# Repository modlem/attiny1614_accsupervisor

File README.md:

# attiny1614_accsupervisor
Relay Service Module Design Files

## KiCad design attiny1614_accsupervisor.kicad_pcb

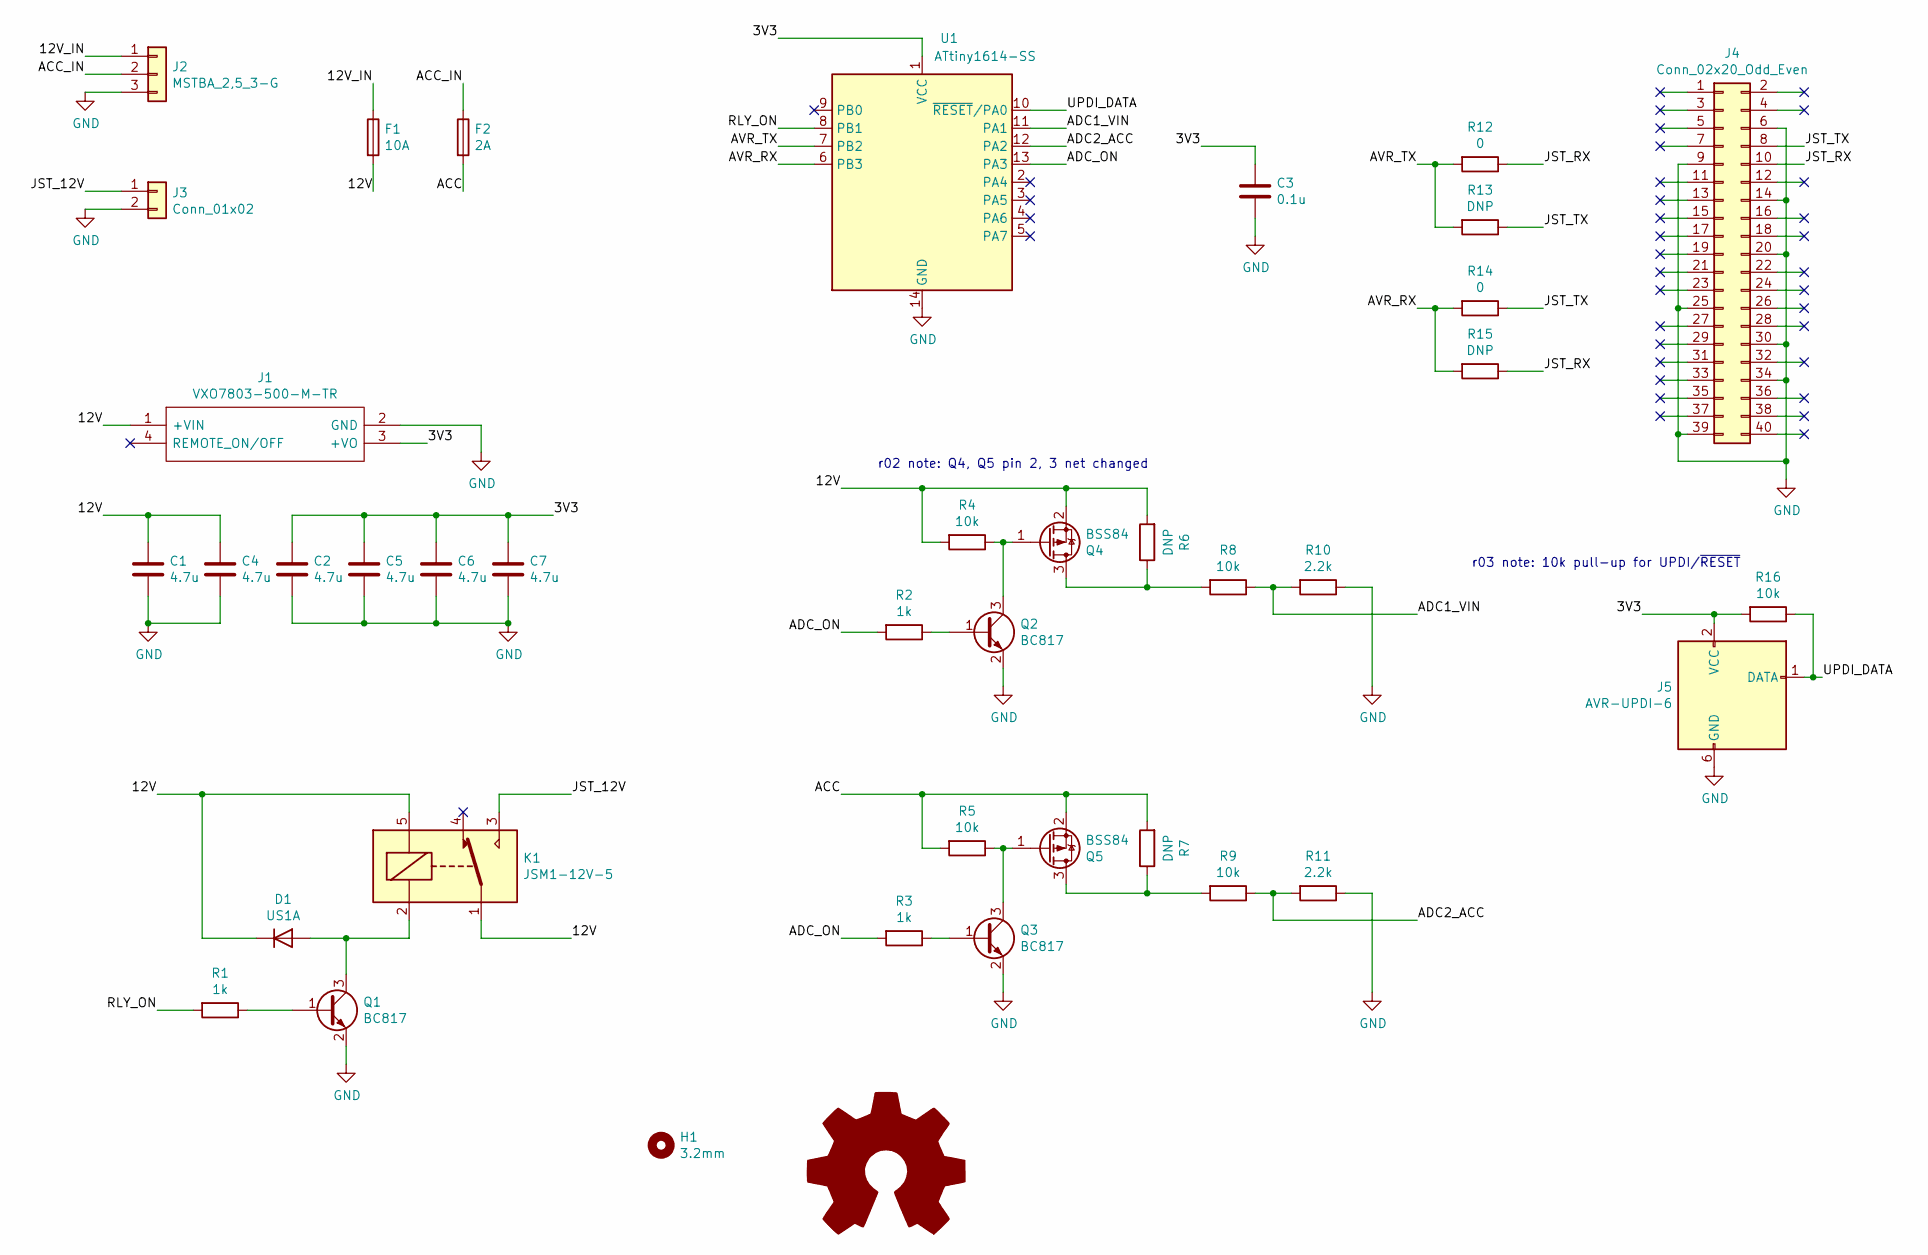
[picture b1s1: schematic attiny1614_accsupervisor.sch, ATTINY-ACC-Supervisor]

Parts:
C1, C2, C4, C5, C6, C7: 4.7u; C_0805_2012Metric_Pad1.15x1.40mm_HandSolder; Manufacturer_Part_Number 0805X475M250CT
C3: 0.1u; C_1206_3216Metric_Pad1.42x1.75mm_HandSolder
D1: US1A; D_SMA; Manufacturer_Part_Number US1A-13-F
F1: 10A; Fuseholder_Cylinder-5x20mm_Geoyoung_GF-205B; Manufacturer_Part_Number (10A)
F2: 2A; Fuseholder_Cylinder-5x20mm_Geoyoung_GF-205B
H1: 3.2mm; MountingHole_3.2mm_M3
J1: VXO7803-500-M-TR; VXO7803500MTR; Mouser Part Number 490-VXO7803-500-M-TR
J2: MSTBA_2,5_3-G; PhoenixContact_MSTBA_2,5_3-G_1x03_P5.00mm_Horizontal
J3: Conn_01x02; TerminalBlock_Phoenix_PT-1,5-2-5.0-H_1x02_P5.00mm_Horizontal
J4: Conn_02x20_Odd_Even; PinHeader_2x20_P2.54mm_Vertical
J5: AVR-UPDI-6; PinHeader_2x03_P2.54mm_Vertical
K1: JSM1-12V-5; Relay_SPDT_Omron-G5LE-1; Manufacturer_Part_Number JSM1-12V-5
Q1, Q2, Q3: BC817; SOT-23; Manufacturer_Part_Number BC817-25,215
Q4, Q5: BSS84; SOT-23; Manufacturer_Part_Number BSS84-7-F
R1, R2, R3: 1k; R_1206_3216Metric_Pad1.42x1.75mm_HandSolder; Manufacturer_Part_Number (1k)
R4, R5, R8, R9, R16: 10k; R_1206_3216Metric_Pad1.42x1.75mm_HandSolder; Manufacturer_Part_Number (10k)
R6, R7, R13, R15: DNP; R_1206_3216Metric_Pad1.42x1.75mm_HandSolder
R10, R11: 2.2k; R_1206_3216Metric_Pad1.42x1.75mm_HandSolder; Manufacturer_Part_Number (2.2k)
R12, R14: 0; R_1206_3216Metric_Pad1.42x1.75mm_HandSolder; Manufacturer_Part_Number (0)
U1: ATtiny1614-SS; SOIC-14_3.9x8.7mm_P1.27mm

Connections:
/3V3: C2.1, C3.1, C5.1, C6.1, C7.1, J1.3 (+VO), J5.2 (VCC), R16.2, U1.1 (VCC)
/12V: C1.1, C4.1, D1.1 (K), F1.2, J1.1 (+VIN), K1.1, K1.5, Q4.2 (S), R4.2, R6.2
/12V_IN: F1.1, J2.1
/ACC: F2.2, Q5.2 (S), R5.2, R7.2
/ACC_IN: F2.1, J2.2
/ADC1_VIN: R8.1, R10.2, U1.11 (PA1)
/ADC2_ACC: R9.1, R11.2, U1.12 (PA2)
/ADC_ON: R2.2, R3.2, U1.13 (PA3)
/AVR_RX: R14.2, R15.2, U1.6 (PB3)
/AVR_TX: R12.2, R13.2, U1.7 (PB2)
/JST_12V: J3.1, K1.3
/JST_RX: J4.10, R12.1, R15.1
/JST_TX: J4.8, R13.1, R14.1
/RLY_ON: R1.2, U1.8 (PB1)
/UPDI_DATA: J5.1 (DATA), R16.1, U1.10 (~RESET~/PA0)
GND: C1.2, C2.2, C3.2, C4.2, C5.2, C6.2, C7.2, J1.2 (GND), J2.3, J3.2, J4.6, J4.9, J4.14, J4.20, J4.25, J4.30, J4.34, J4.39, J5.6 (GND), Q1.2 (E), Q2.2 (E), Q3.2 (E), R10.1, R11.1, U1.14 (GND)
unnamed: D1.2 (A), K1.2, Q1.3 (C)
unnamed: Q1.1 (B), R1.1
unnamed: Q2.1 (B), R2.1
unnamed: Q2.3 (C), Q4.1 (G), R4.1
unnamed: Q3.1 (B), R3.1
unnamed: Q3.3 (C), Q5.1 (G), R5.1
unnamed: Q4.3 (D), R6.1, R8.2
unnamed: Q5.3 (D), R7.1, R9.2

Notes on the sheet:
r02 note: Q4, Q5 pin 2, 3 net changed
r03 note: 10k pull-up for UPDI/~RESET

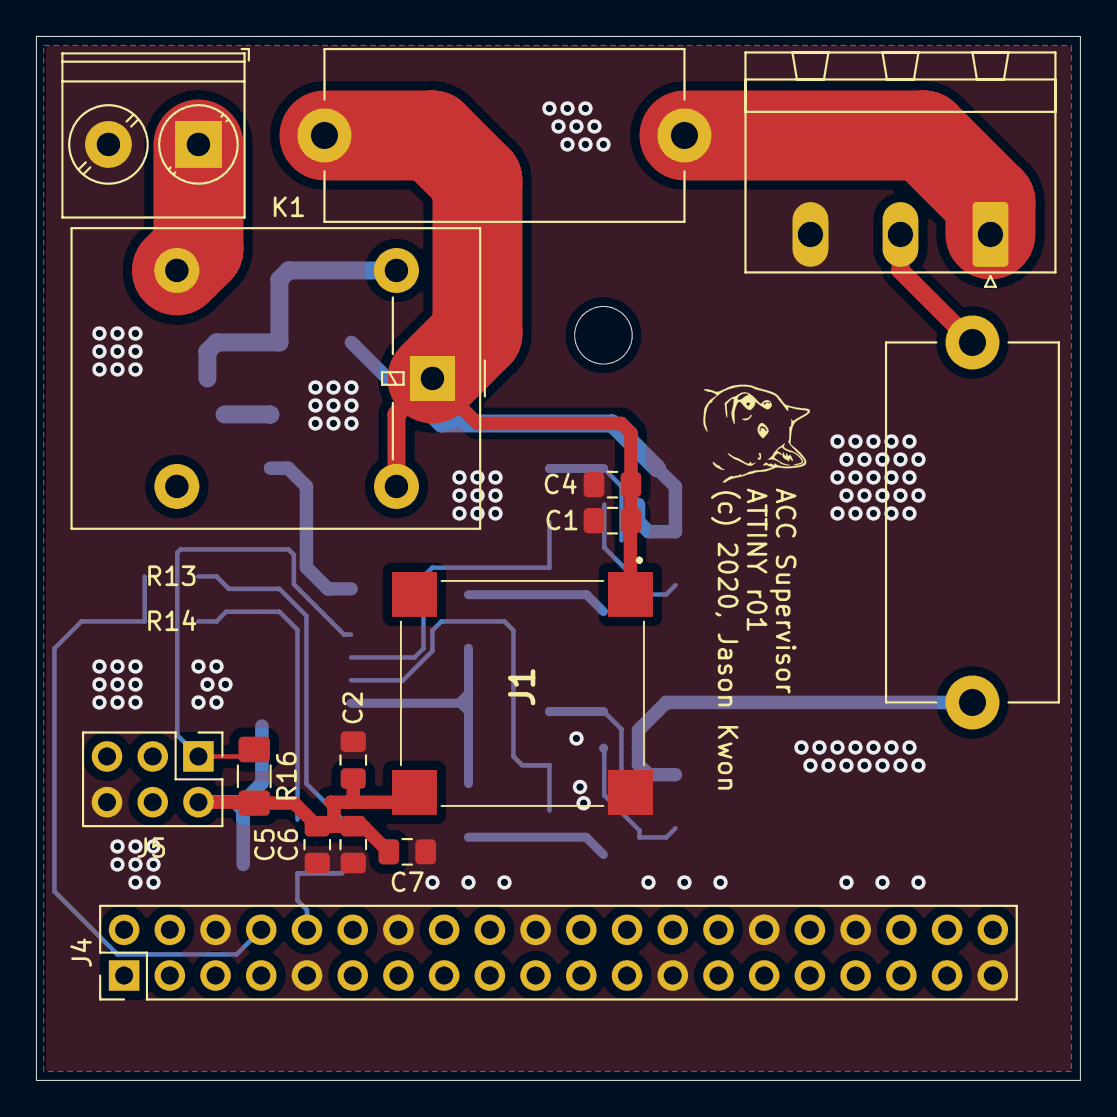
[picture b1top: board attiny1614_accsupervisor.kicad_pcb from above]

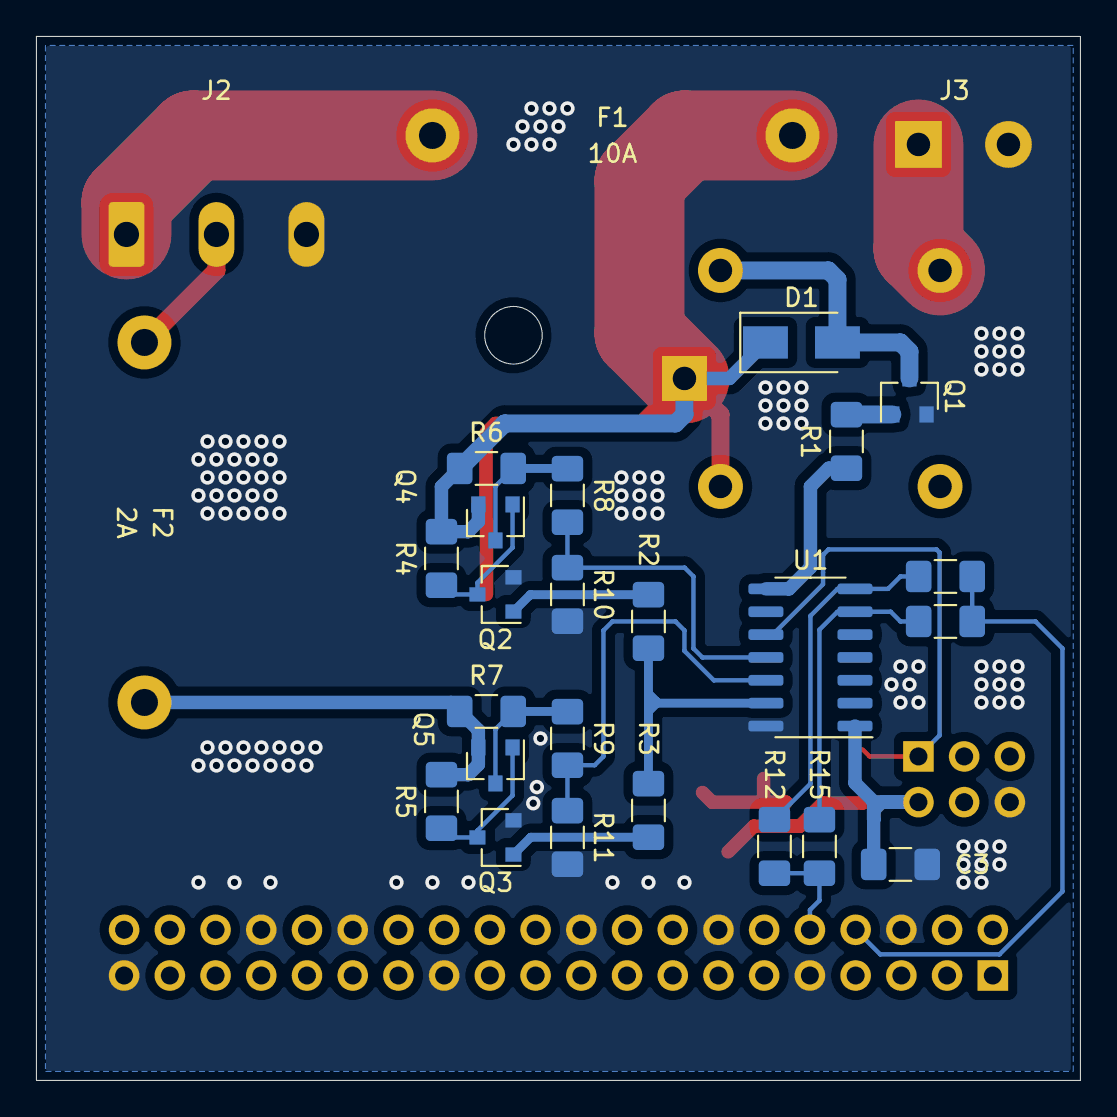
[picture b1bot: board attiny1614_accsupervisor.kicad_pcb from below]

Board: 2 copper layers, 58.0 x 58.0 mm, 39 parts (23 on the bottom side), 24 nets.

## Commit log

2020-08-31 1614 and relay added
2020-08-31 VXO7803 library added
2020-08-31 Library settings changed
2020-08-31 UPDI, JST hdrs added
2020-09-01 Netlist generated
2020-09-01 First layout
2020-09-02 r01 gerber generated
2020-09-02 Layout done
2020-09-02 BOM consolidation, 10/22uF to 4.7uFs
2020-09-02 Gerber generated, r01
2020-09-02 Doge silk
2020-09-22 Q4, Q5 PFETs pin swap fixed
    P ch. MOSFETs drain-source swapped pins are now fixed
2020-09-22 UPDI_DATA/~RESET pullup added
    10k pullup for UPDI_DATA/~RESET pin added

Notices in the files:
attiny1614_accsupervisor.kicad_pcb:
(c) 2020, Jason Kwon
